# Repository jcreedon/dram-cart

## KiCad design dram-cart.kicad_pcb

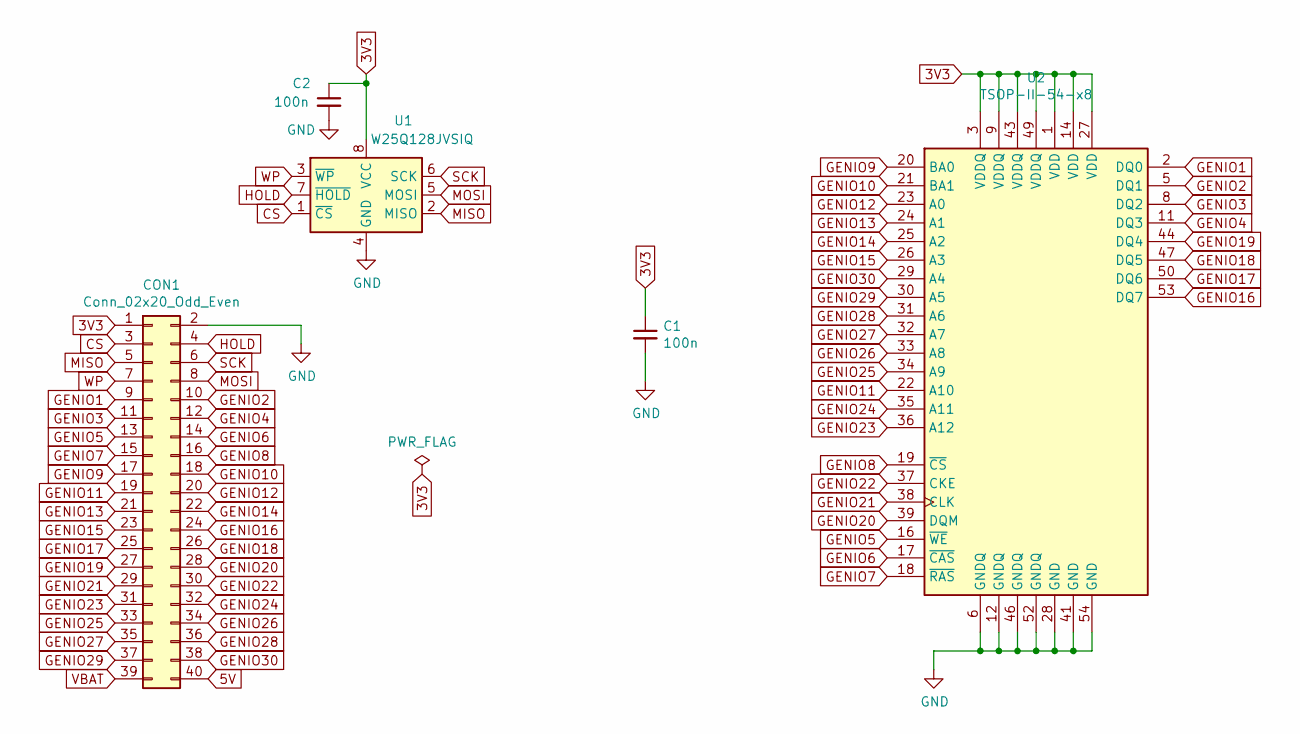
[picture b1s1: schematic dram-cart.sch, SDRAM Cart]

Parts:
C1, C2: 100n; C_0603_1608Metric
CON1: Conn_02x20_Odd_Even; PinHeader_2x20_P2.54mm_Horizontal_Mirrored
U1: W25Q128JVSIQ; SSOP-8_5.25x5.24mm_P1.27mm
U2: TSOP-II-54-x8; TSOP-II-54_22.2x10.16mm_P0.8mm

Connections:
3V3: C1.1, C2.1, CON1.1, U1.8 (VCC), U2.1 (VDD), U2.3 (VDDQ), U2.9 (VDDQ), U2.14 (VDD), U2.27 (VDD), U2.43 (VDDQ), U2.49 (VDDQ)
CS: CON1.3, U1.1 (~CS)
GENIO1: CON1.9, U2.2 (DQ0)
GENIO2: CON1.10, U2.5 (DQ1)
GENIO3: CON1.11, U2.8 (DQ2)
GENIO4: CON1.12, U2.11 (DQ3)
GENIO5: CON1.13, U2.16 (~WE)
GENIO6: CON1.14, U2.17 (~CAS)
GENIO7: CON1.15, U2.18 (~RAS)
GENIO8: CON1.16, U2.19 (~CS)
GENIO9: CON1.17, U2.20 (BA0)
GENIO10: CON1.18, U2.21 (BA1)
GENIO11: CON1.19, U2.22 (A10)
GENIO12: CON1.20, U2.23 (A0)
GENIO13: CON1.21, U2.24 (A1)
GENIO14: CON1.22, U2.25 (A2)
GENIO15: CON1.23, U2.26 (A3)
GENIO16: CON1.24, U2.53 (DQ7)
GENIO17: CON1.25, U2.50 (DQ6)
GENIO18: CON1.26, U2.47 (DQ5)
GENIO19: CON1.27, U2.44 (DQ4)
GENIO20: CON1.28, U2.39 (DQM)
GENIO21: CON1.29, U2.38 (CLK)
GENIO22: CON1.30, U2.37 (CKE)
GENIO23: CON1.31, U2.36 (A12)
GENIO24: CON1.32, U2.35 (A11)
GENIO25: CON1.33, U2.34 (A9)
GENIO26: CON1.34, U2.33 (A8)
GENIO27: CON1.35, U2.32 (A7)
GENIO28: CON1.36, U2.31 (A6)
GENIO29: CON1.37, U2.30 (A5)
GENIO30: CON1.38, U2.29 (A4)
GND: C1.2, C2.2, CON1.2, U1.4 (GND), U2.6 (GNDQ), U2.12 (GNDQ), U2.28 (GND), U2.41 (GND), U2.46 (GNDQ), U2.52 (GNDQ), U2.54 (GND)
HOLD: CON1.4, U1.7 (~HOLD)
MISO: CON1.5, U1.2 (MISO)
MOSI: CON1.8, U1.5 (MOSI)
SCK: CON1.6, U1.6 (SCK)
WP: CON1.7, U1.3 (~WP)

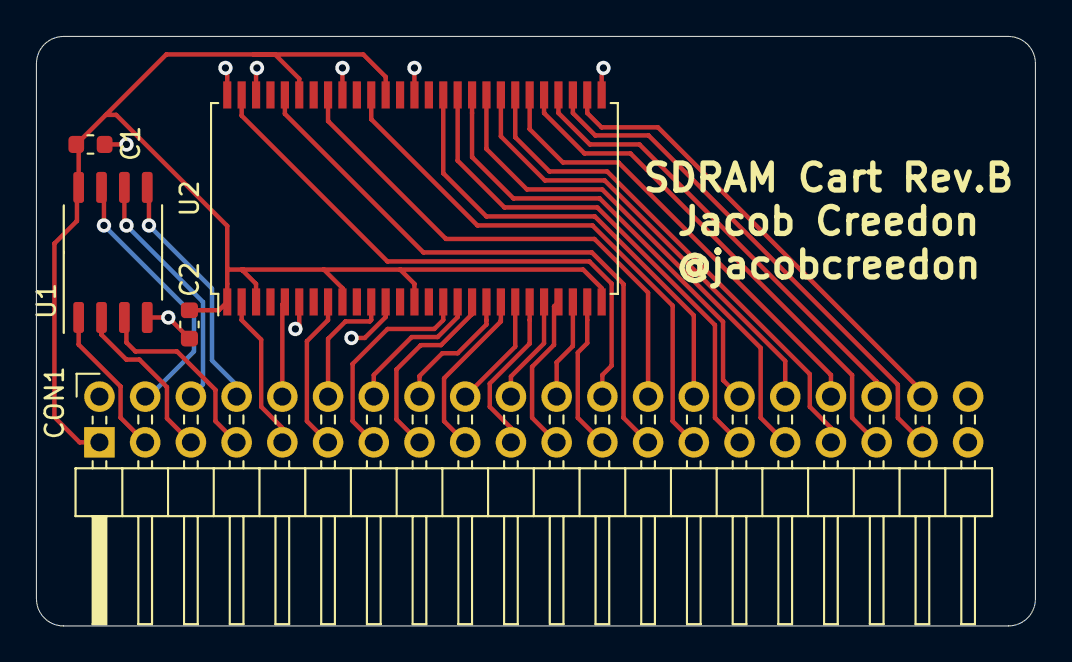
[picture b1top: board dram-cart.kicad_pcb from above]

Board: 2 copper layers, 55.5 x 32.8 mm, 5 parts (0 on the bottom side), 38 nets.

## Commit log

2019-11-09 Add gitignore
2019-11-09 First version
2019-11-21 Add new RAM schematic symbol library
2019-11-21 Rev.B of Schematic and PCB
    This corrects errors in Rev.A where the wrong pins were used for some DQ signals.
2019-11-21 Add mapping file
    This adds a quick text document showing which signals map to which pins.
